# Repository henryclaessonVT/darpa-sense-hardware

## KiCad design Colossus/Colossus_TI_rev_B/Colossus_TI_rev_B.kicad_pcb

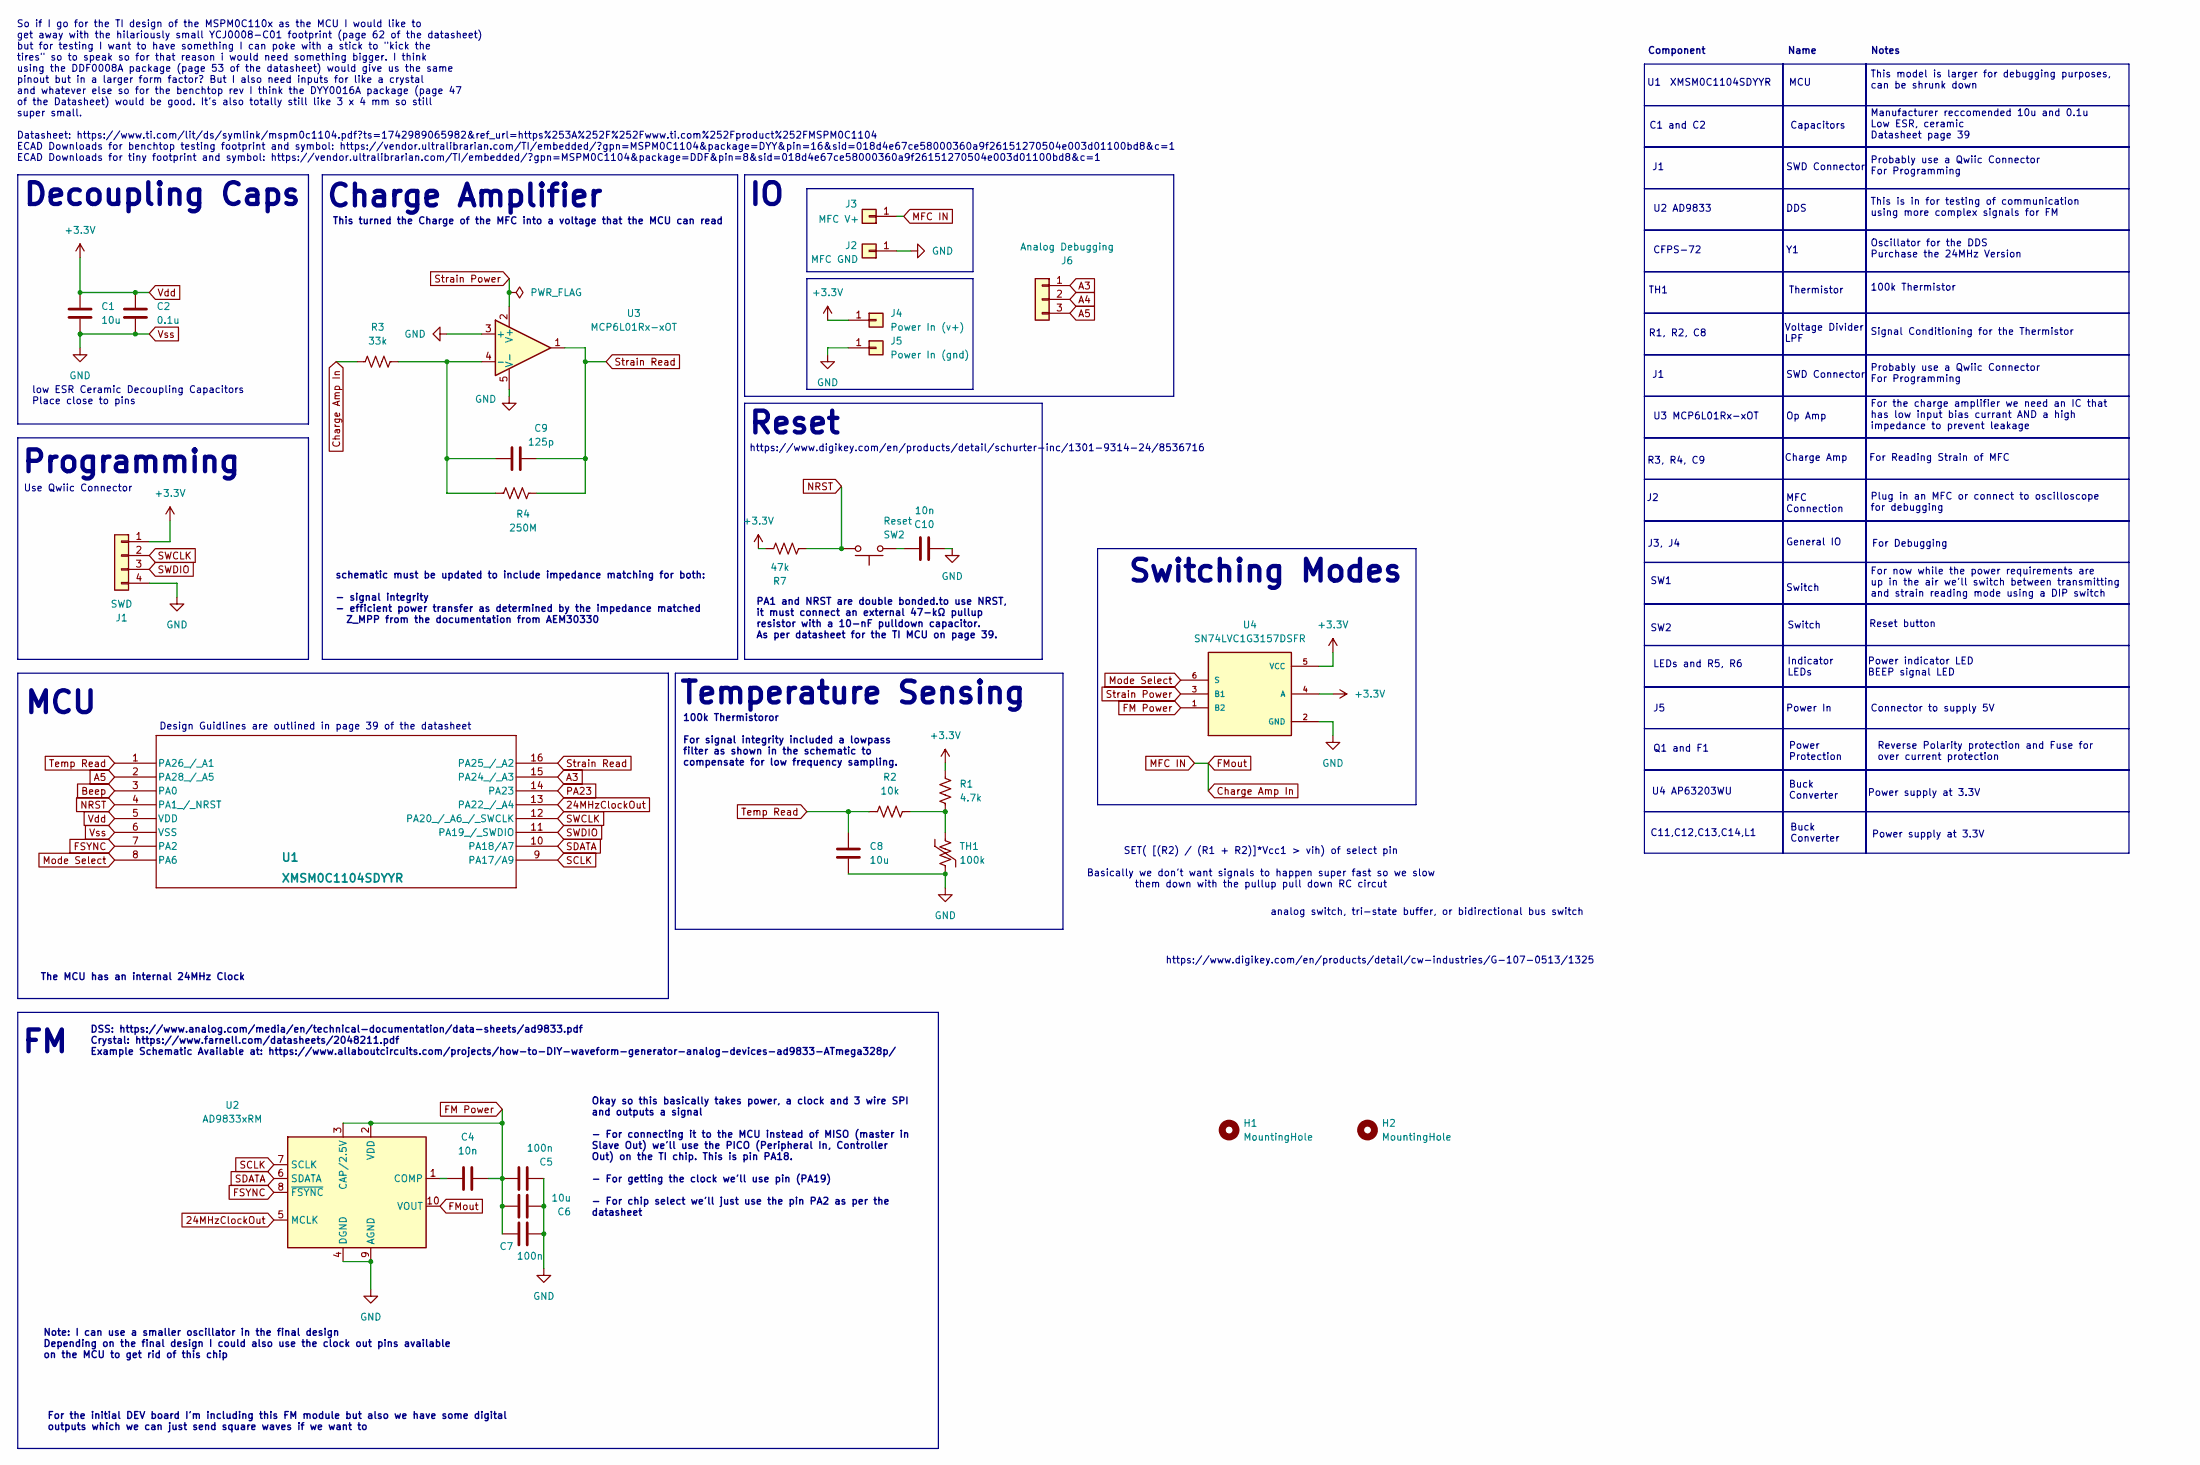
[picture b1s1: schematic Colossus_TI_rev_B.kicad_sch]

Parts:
C1, C6, C8: 10u; C_0402_1005Metric
C2: 0.1u; C_0201_0603Metric
C4: 10n; C_0201_0603Metric
C5, C7: 100n; C_0201_0603Metric
C9: 125p; C_0201_0603Metric
C10: 10n; C_0805_2012Metric
H1, H2: MountingHole; MountingHole_2.2mm_M2_Pad_Via
J1: SWD; PinHeader_1x04_P2.54mm_Vertical
J2: MFC GND; TestPoint_Pad_2.0x2.0mm
J3: MFC V+; TestPoint_Pad_2.0x2.0mm
J4: Power In (v+); TestPoint_Pad_2.0x2.0mm
J5: Power In (gnd); TestPoint_Pad_2.0x2.0mm
J6: Analog Debugging; PinSocket_1x03_P2.54mm_Vertical
R1: 4.7k; R_0201_0603Metric
R2: 10k; R_0201_0603Metric
R3: 33k; R_0201_0603Metric
R4: 250M; R_0402_1005Metric
R7: 47k; R_0805_2012Metric
SW2: Reset; SW_B3F-1000_OMR
TH1: 100k; R_0402_1005Metric
U1: XMSM0C1104SDYYR; SOT-23-THIN16_DYY_TEX
U2: AD9833xRM; MSOP-10_3x3mm_P0.5mm
U3: MCP6L01Rx-xOT; SOT-23-5
U4: SN74LVC1G3157DSFR; SON35P100X100X40-6N; PARTREV M

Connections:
24MHzClockOut: U1.13 (PA22_/_A4), U2.5 (MCLK)
A3: J6.1, U1.15 (PA24_/_A3)
A4: J6.2
A5: J6.3, U1.2 (PA28_/_A5)
Beep: U1.3 (PA0)
Charge Amp In: J3.1, R3.1, U2.10 (VOUT)
FM Power: C4.2, C5.2, C6.2, C7.1, U2.2 (VDD), U2.3 (CAP/2.5V), U4.1 (B2)
FSYNC: U1.7 (PA2), U2.8 (~FSYNC)
Mode Select: U1.8 (PA6), U4.6 (S)
NRST: R7.2, SW2.2, U1.4 (PA1_/_NRST)
unnamed: C10.2, SW2.1
unnamed: R1.2, R2.2, TH1.2
unnamed: C4.1, U2.1 (COMP)
unnamed: C9.1, R3.2, R4.1, U3.4 (-)
PA23: U1.14 (PA23)
SCLK: U1.9 (PA17/A9), U2.7 (SCLK)
SDATA: U1.10 (PA18/A7), U2.6 (SDATA)
SWCLK: J1.2, U1.12 (PA20_/_A6_/_SWCLK)
SWDIO: J1.3, U1.11 (PA19_/_SWDIO)
Strain Power: U3.2 (V+), U4.3 (B1)
Strain Read: C9.2, R4.2, U1.16 (PA25_/_A2), U3.1
Temp Read: C8.2, R2.1, U1.1 (PA26_/_A1)
Vdd: C1.1, C2.1, J1.1, J4.1, R1.1, R7.1, U1.5 (VDD), U4.4 (A), U4.5 (VCC)
Vss: C1.2, C2.2, C5.1, C6.1, C7.2, C8.1, C10.1, J1.4, J2.1, J5.1, TH1.1, U1.6 (VSS), U2.4 (DGND), U2.9 (AGND), U3.3 (+), U3.5 (V-), U4.2 (GND)

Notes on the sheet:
J3, J4
TH1
Buck Converter
DDS
For the initial DEV board I'm including this FM module but also we have some digital outputs which we can just send square waves if we want to
Notes
Power supply at 3.3V
Charge Amp
Design Guidlines are outlined in page 39 of the datasheet
Note: I can use a smaller oscillator in the final design Depending on the final design I could also use the clock out pins available on the MCU to get rid of this chip
Switch
low ESR Ceramic Decoupling Capacitors Place close to pins
C1 and C2
For the charge amplifier we need an IC that has low input bias currant AND a high impedance to prevent leakage
Power indicator LED BEEP signal LED
Temperature Sensing
Plug in an MFC or connect to oscilloscope for debugging
Voltage Divider LPF
U4 AP63203WU
General IO
Power Protection
analog switch, tri-state buffer, or bidirectional bus switch
Probably use a Qwiic Connector For Programming
For now while the power requirements are up in the air we'll switch between transmitting and strain reading mode using a DIP switch
Programming
U2 AD9833
Charge Amplifier
Manufacturer reccomended 10u and 0.1u Low ESR, ceramic Datasheet page 39
This turned the Charge of the MFC into a voltage that the MCU can read
schematic must be updated to include impedance matching for both: - signal integrity - efficient power transfer as determined by the impedance matched Z_MPP from the documentation from AEM30330
Switching Modes
Name
Power In
C11,C12,C13,C14,L1
Decoupling Caps
Capacitors
Connector to supply 5V
Use Qwiic Connector
SET( [(R2) / (R1 + R2)]*Vcc1 > vih) of select pin Basically we don't want signals to happen super fast so we slow them down with the pullup pull down RC circut
Component

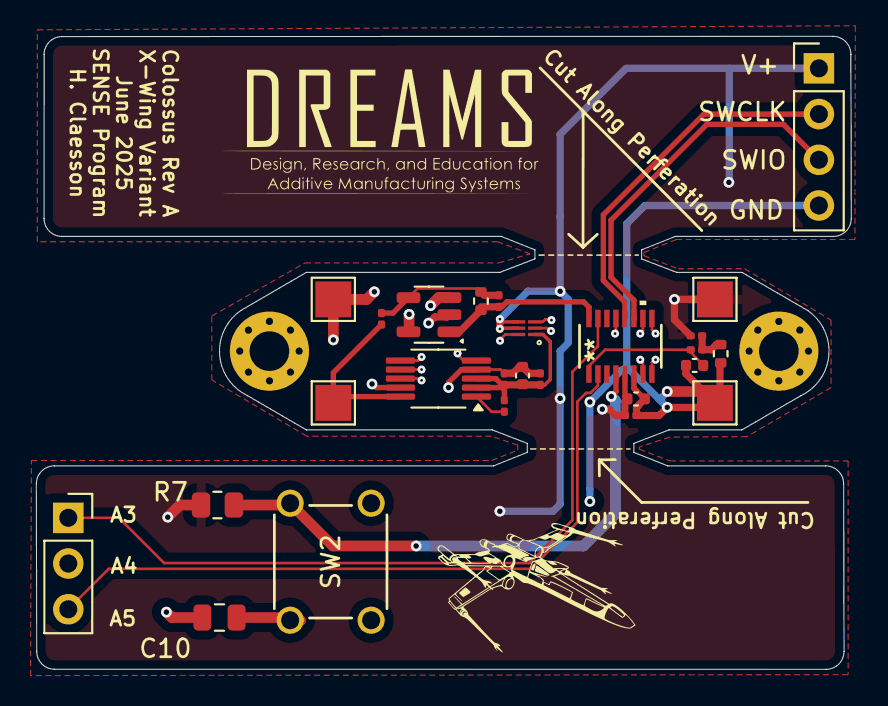
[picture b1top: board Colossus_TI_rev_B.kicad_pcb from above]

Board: 4 copper layers, 45.3 x 35.2 mm, 28 parts (0 on the bottom side), 21 nets.

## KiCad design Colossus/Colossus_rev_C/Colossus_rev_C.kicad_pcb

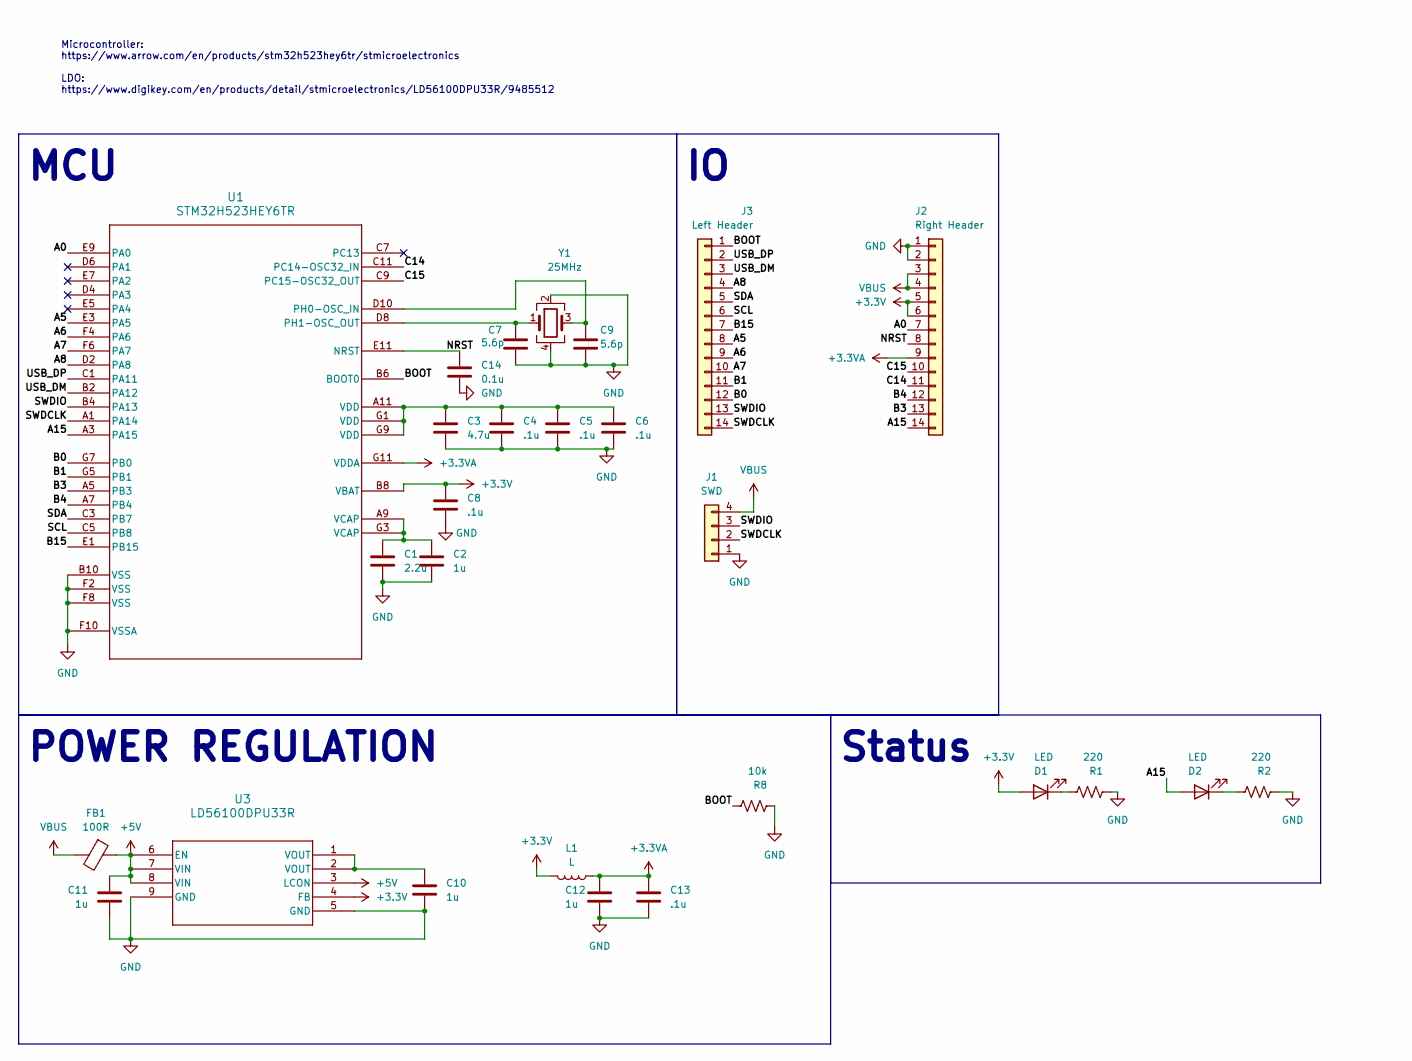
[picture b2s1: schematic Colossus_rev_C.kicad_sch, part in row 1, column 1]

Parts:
C1: 2.2u; C_0201_0603Metric
C2, C10, C11, C12: 1u; C_0201_0603Metric
C3: 4.7u; C_0201_0603Metric
C4, C5, C6, C8, C13: .1u; C_0201_0603Metric
C7, C9: 5.6p; C_0201_0603Metric
C14: 0.1u; C_0201_0603Metric
D1, D2: LED; LED_0201_0603Metric
FB1: 100R; LED_0201_0603Metric
J1: SWD; PinHeader_1x04_P1.00mm_Vertical
J2: Right Header; PinHeader_1x14_P1.27mm_Vertical
J3: Left Header; PinHeader_1x14_P1.27mm_Vertical
L1: L; L_0201_0603Metric
R1, R2: 220; R_01005_0402Metric
R8: 10k; R_01005_0402Metric
U1: STM32H523HEY6TR; WLCSP39_STM
U3: LD56100DPU33R; DFN8_1P6X1P2_STM-M
Y1: 25MHz; Oscillator_SMD_Abracon_ASCO-4Pin_1.6x1.2mm

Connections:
+3.3V: C8.1, D1.2 (A), J2.5, J2.6, L1.2, U1.B8 (VBAT), U3.4 (FB)
+3.3VA: C12.1, C13.1, J2.9, L1.1, U1.G11 (VDDA)
+5V: C11.1, FB1.1, U3.3 (LCON), U3.6 (EN), U3.7 (VIN), U3.8 (VIN)
/A0: J2.7, U1.E9 (PA0)
/A5: J3.8, U1.E3 (PA5)
/A6: J3.9, U1.F4 (PA6)
/A7: J3.10, U1.F6 (PA7)
/A8: J3.4, U1.D2 (PA8)
/A15: D2.2 (A), J2.14, U1.A3 (PA15)
/B0: J3.12, U1.G7 (PB0)
/B1: J3.11, U1.G5 (PB1)
/B3: J2.13, U1.A5 (PB3)
/B4: J2.12, U1.A7 (PB4)
/B15: J3.7, U1.E1 (PB15)
/BOOT: J3.1, R8.1, U1.B6 (BOOT0)
/C14: J2.11, U1.C11 (PC14-OSC32_IN)
/C15: J2.10, U1.C9 (PC15-OSC32_OUT)
/NRST: C14.1, J2.8, U1.E11 (NRST)
/SCL: J3.6, U1.C5 (PB8)
/SDA: J3.5, U1.C3 (PB7)
/SWDCLK: J1.2, J3.14, U1.A1 (PA14)
/SWDIO: J1.3, J3.13, U1.B4 (PA13)
/USB_DM: J3.3, U1.B2 (PA12)
/USB_DP: J3.2, U1.C1 (PA11)
GND: C1.2, C2.2, C3.2, C4.2, C5.2, C6.2, C7.2, C8.2, C9.2, C10.2, C11.2, C12.2, C13.2, C14.2, J1.1, J2.1, J2.2, R1.2, R2.2, R8.2, U1.B10 (VSS), U1.F2 (VSS), U1.F8 (VSS), U1.F10 (VSSA), U3.5 (GND), U3.9 (GND), Y1.2, Y1.4
unnamed: C1.1, C2.1, U1.A9 (VCAP), U1.G3 (VCAP)
unnamed: C3.1, C4.1, C5.1, C6.1, U1.A11 (VDD), U1.G1 (VDD), U1.G9 (VDD)
unnamed: C10.1, U3.1 (VOUT), U3.2 (VOUT)
unnamed: D1.1 (K), R1.1
unnamed: D2.1 (K), R2.1
unnamed: C9.1, U1.D10 (PH0-OSC_IN), Y1.3
unnamed: C7.1, U1.D8 (PH1-OSC_OUT), Y1.1
VBUS: FB1.2, J1.4, J2.3, J2.4

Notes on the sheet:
TODO: x Temperature Sensing Circuit o Strain Sensing Circuit -- skip this rev x IMU Circuit - MFC Communication Out Circuit - MFC Communication In Circuit - Energy Harvesting Circuit After that -- layout
Microcontroller: https://www.arrow.com/en/products/stm32h523hey6tr/stmicroelectronics LDO: https://www.digikey.com/en/products/detail/stmicroelectronics/LD56100DPU33R/9485512
MCU
POWER REGULATION
Status

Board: 2 copper layers, 27 parts (0 on the bottom side), 33 nets, no tracks yet.

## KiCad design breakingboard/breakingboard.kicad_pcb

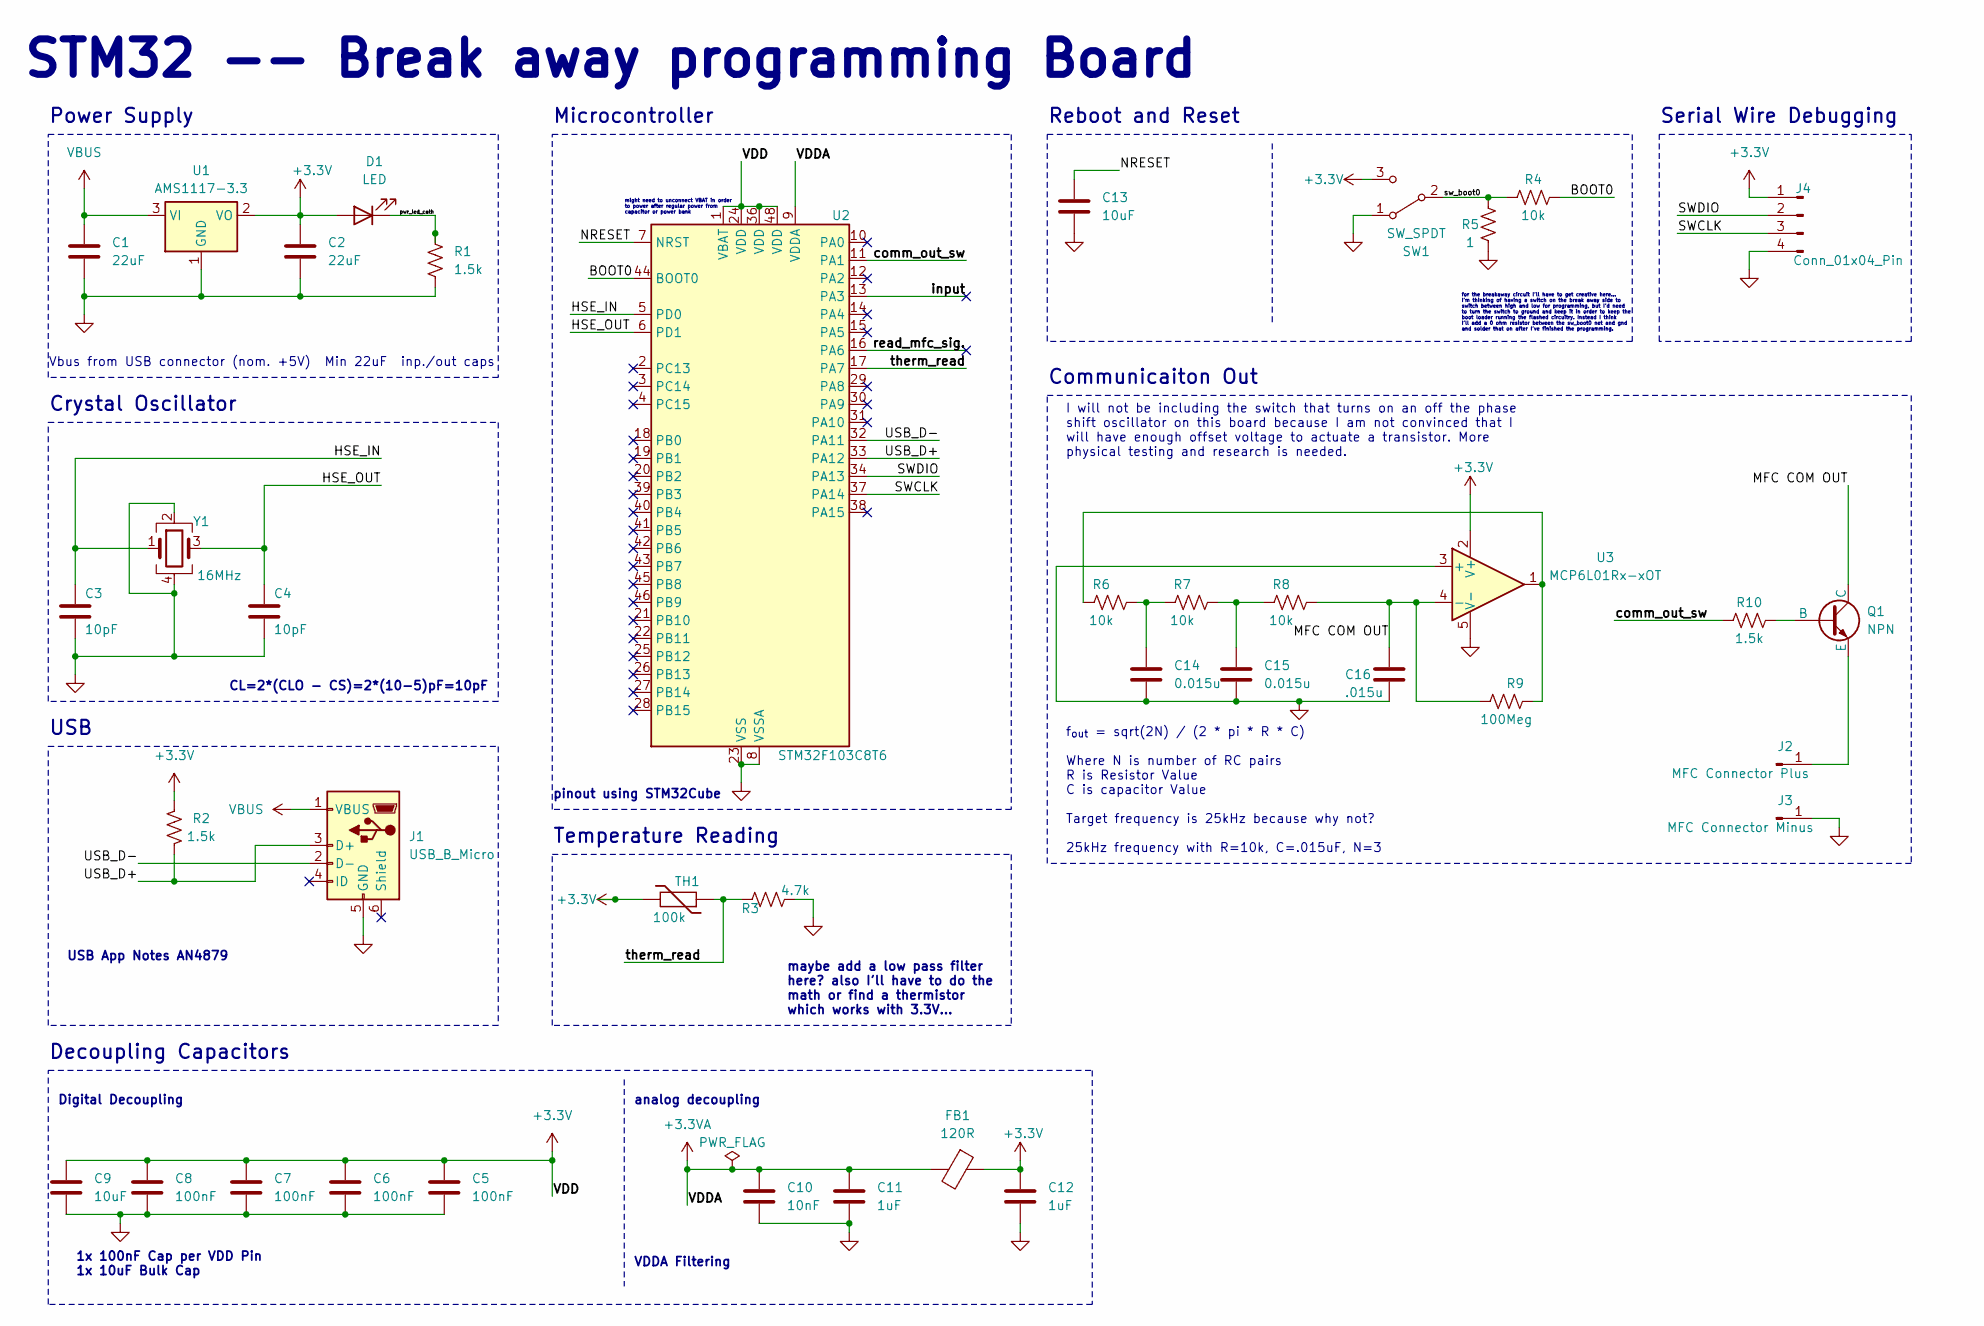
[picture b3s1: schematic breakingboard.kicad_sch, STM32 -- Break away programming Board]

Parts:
C1, C2: 22uF; C_0805_2012Metric
C3, C4: 10pF; C_0402_1005Metric
C5, C6, C7, C8: 100nF; C_0402_1005Metric
C9, C13: 10uF; C_0603_1608Metric
C10: 10nF; C_0402_1005Metric
C11, C12: 1uF; C_0402_1005Metric
C14, C15: 0.015u; C_0402_1005Metric
C16: .015u; C_0402_1005Metric
D1: LED; LED_0402_1005Metric
FB1: 120R; L_0603_1608Metric
J1: USB_B_Micro; USB_Micro-B_Wuerth_629105150521
J2: MFC Connector Plus; SolderWire-0.1sqmm_1x01_D0.4mm_OD1mm
J3: MFC Connector Minus; SolderWire-0.1sqmm_1x01_D0.4mm_OD1mm
J4: Conn_01x04_Pin; PinHeader_1x04_P2.54mm_Vertical
Q1: NPN; SOT-23
R1, R2, R10: 1.5k; R_0402_1005Metric
R3: 4.7k; R_0402_1005Metric
R4, R6, R7, R8: 10k; R_0402_1005Metric
R5: 1; R_0402_1005Metric
R9: 100Meg; R_0402_1005Metric
SW1: SW_SPDT; SW_SPDT_PCM12
TH1: 100k; R_0402_1005Metric
U1: AMS1117-3.3; SOT-223-3_TabPin2
U2: STM32F103C8T6; LQFP-48_7x7mm_P0.5mm
U3: MCP6L01Rx-xOT; SOT-23-5
Y1: 16MHz; Crystal_SMD_3225-4Pin_3.2x2.5mm

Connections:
+3.3V: C2.1, C5.1, C6.1, C7.1, C8.1, C9.1, C12.1, D1.2 (A), FB1.1, J4.1, R2.2, SW1.3 (C), TH1.2, U1.2 (VO), U2.1 (VBAT), U2.24 (VDD), U2.36 (VDD), U2.48 (VDD), U3.2 (V+)
+3.3VA: C10.1, C11.1, FB1.2, U2.9 (VDDA)
/BOOT0: R4.2, U2.44 (BOOT0)
/HSE_IN: C3.1, U2.5 (PD0), Y1.1
/HSE_OUT: C4.1, U2.6 (PD1), Y1.3
/MFC COM OUT: C16.1, Q1.1 (C), R8.2, R9.1, U3.4 (-)
/NRESET: C13.1, U2.7 (NRST)
/SWCLK: J4.3, U2.37 (PA14)
/SWDIO: J4.2, U2.34 (PA13)
/USB_D+: J1.3 (D+), R2.1, U2.33 (PA12)
/USB_D-: J1.2 (D-), U2.32 (PA11)
/comm_out_sw: R10.1, U2.11 (PA1)
/input: U2.13 (PA3)
/pwr_led_cath: D1.1 (K), R1.1
/read_mfc_sig.: U2.16 (PA6)
/sw_boot0: R4.1, R5.2, SW1.2 (B)
/therm_read: R3.2, TH1.1, U2.17 (PA7)
GND: C1.2, C2.2, C3.2, C4.2, C5.2, C6.2, C7.2, C8.2, C9.2, C10.2, C11.2, C12.2, C13.2, C14.2, C15.2, C16.2, J1.5 (GND), J3.1, J4.4, R1.2, R3.1, R5.1, SW1.1 (A), U1.1 (GND), U2.8 (VSSA), U2.23 (VSS), U2.35 (VSS), U2.47 (VSS), U3.3 (+), U3.5 (V-), Y1.2, Y1.4
unnamed: C14.1, R6.2, R7.1
unnamed: C15.1, R7.2, R8.1
unnamed: J2.1, Q1.3 (E)
unnamed: Q1.2 (B), R10.2
unnamed: R6.1, R9.2, U3.1
VBUS: C1.1, J1.1 (VBUS), U1.3 (VI)

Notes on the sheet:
VDDA Filtering
might need to unconnect VBAT in order to power after regular power from capacitor or power bank
CL=2*(CLO - CS)=2*(10-5)pF=10pF
Microcontroller
Temperature Reading
Serial Wire Debugging
maybe add a low pass filter here? also I'll have to do the math or find a thermistor which works with 3.3V...
Reboot and Reset
I will not be including the switch that turns on an off the phase shift oscillator on this board because I am not convinced that I will have enough offset voltage to actuate a transistor. More physical testing and research is needed.
Communicaiton Out
Decoupling Capacitors
for the breakaway circuit I'll have to get creative here... I'm thinking of having a switch on the break away side to switch between high and low for programming, but I'd need to turn the switch to ground and keep it in order to keep the boot loader running the flashed circuitry. Instead I think I'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
f_{out} = sqrt(2N) / (2 * pi * R * C) Where N is number of RC pairs R is Resistor Value C is capacitor Value Target frequency is 25kHz because why not? 25kHz frequency with R=10k, C=.015uF, N=3
pinout using STM32Cube
Crystal Oscillator
Power Supply
1x 100nF Cap per VDD Pin 1x 10uF Bulk Cap
STM32 -- Break away programming Board
Digital Decoupling
analog decoupling
USB
Vbus from USB connector (nom. +5V) Min 22uF inp./out caps
USB App Notes AN4879

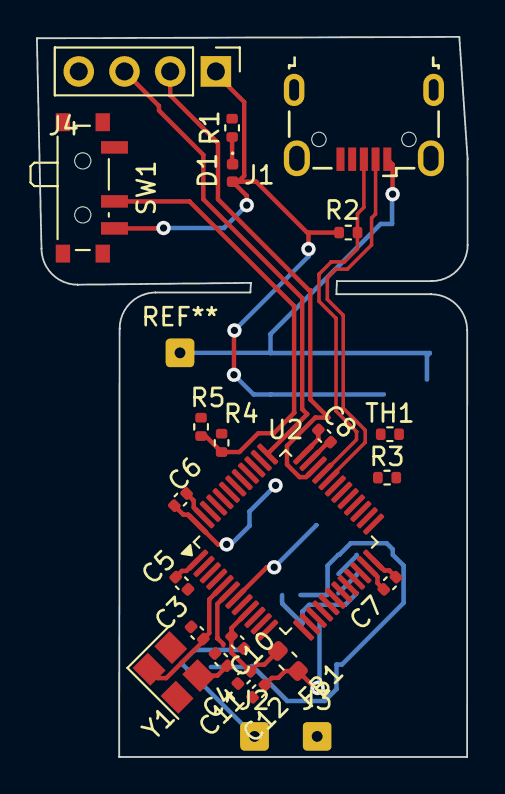
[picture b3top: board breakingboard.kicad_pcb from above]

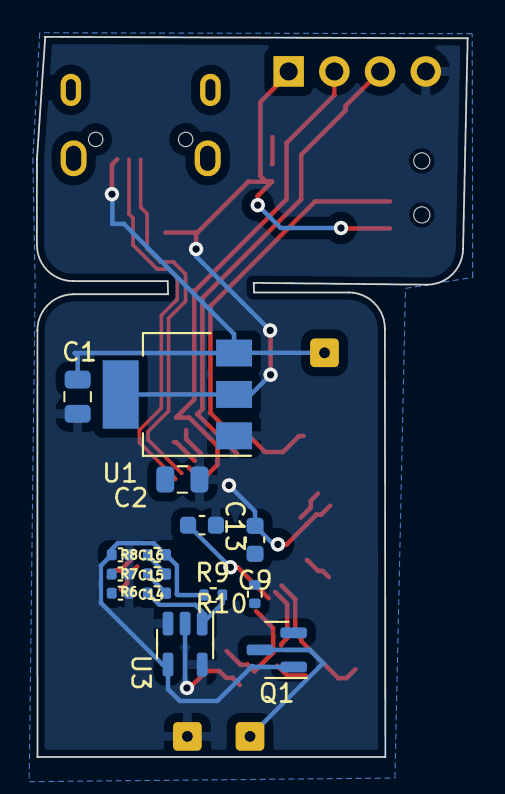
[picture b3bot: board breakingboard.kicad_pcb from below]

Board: 2 copper layers, 23.9 x 40.0 mm, 39 parts (15 on the bottom side), 22 nets.

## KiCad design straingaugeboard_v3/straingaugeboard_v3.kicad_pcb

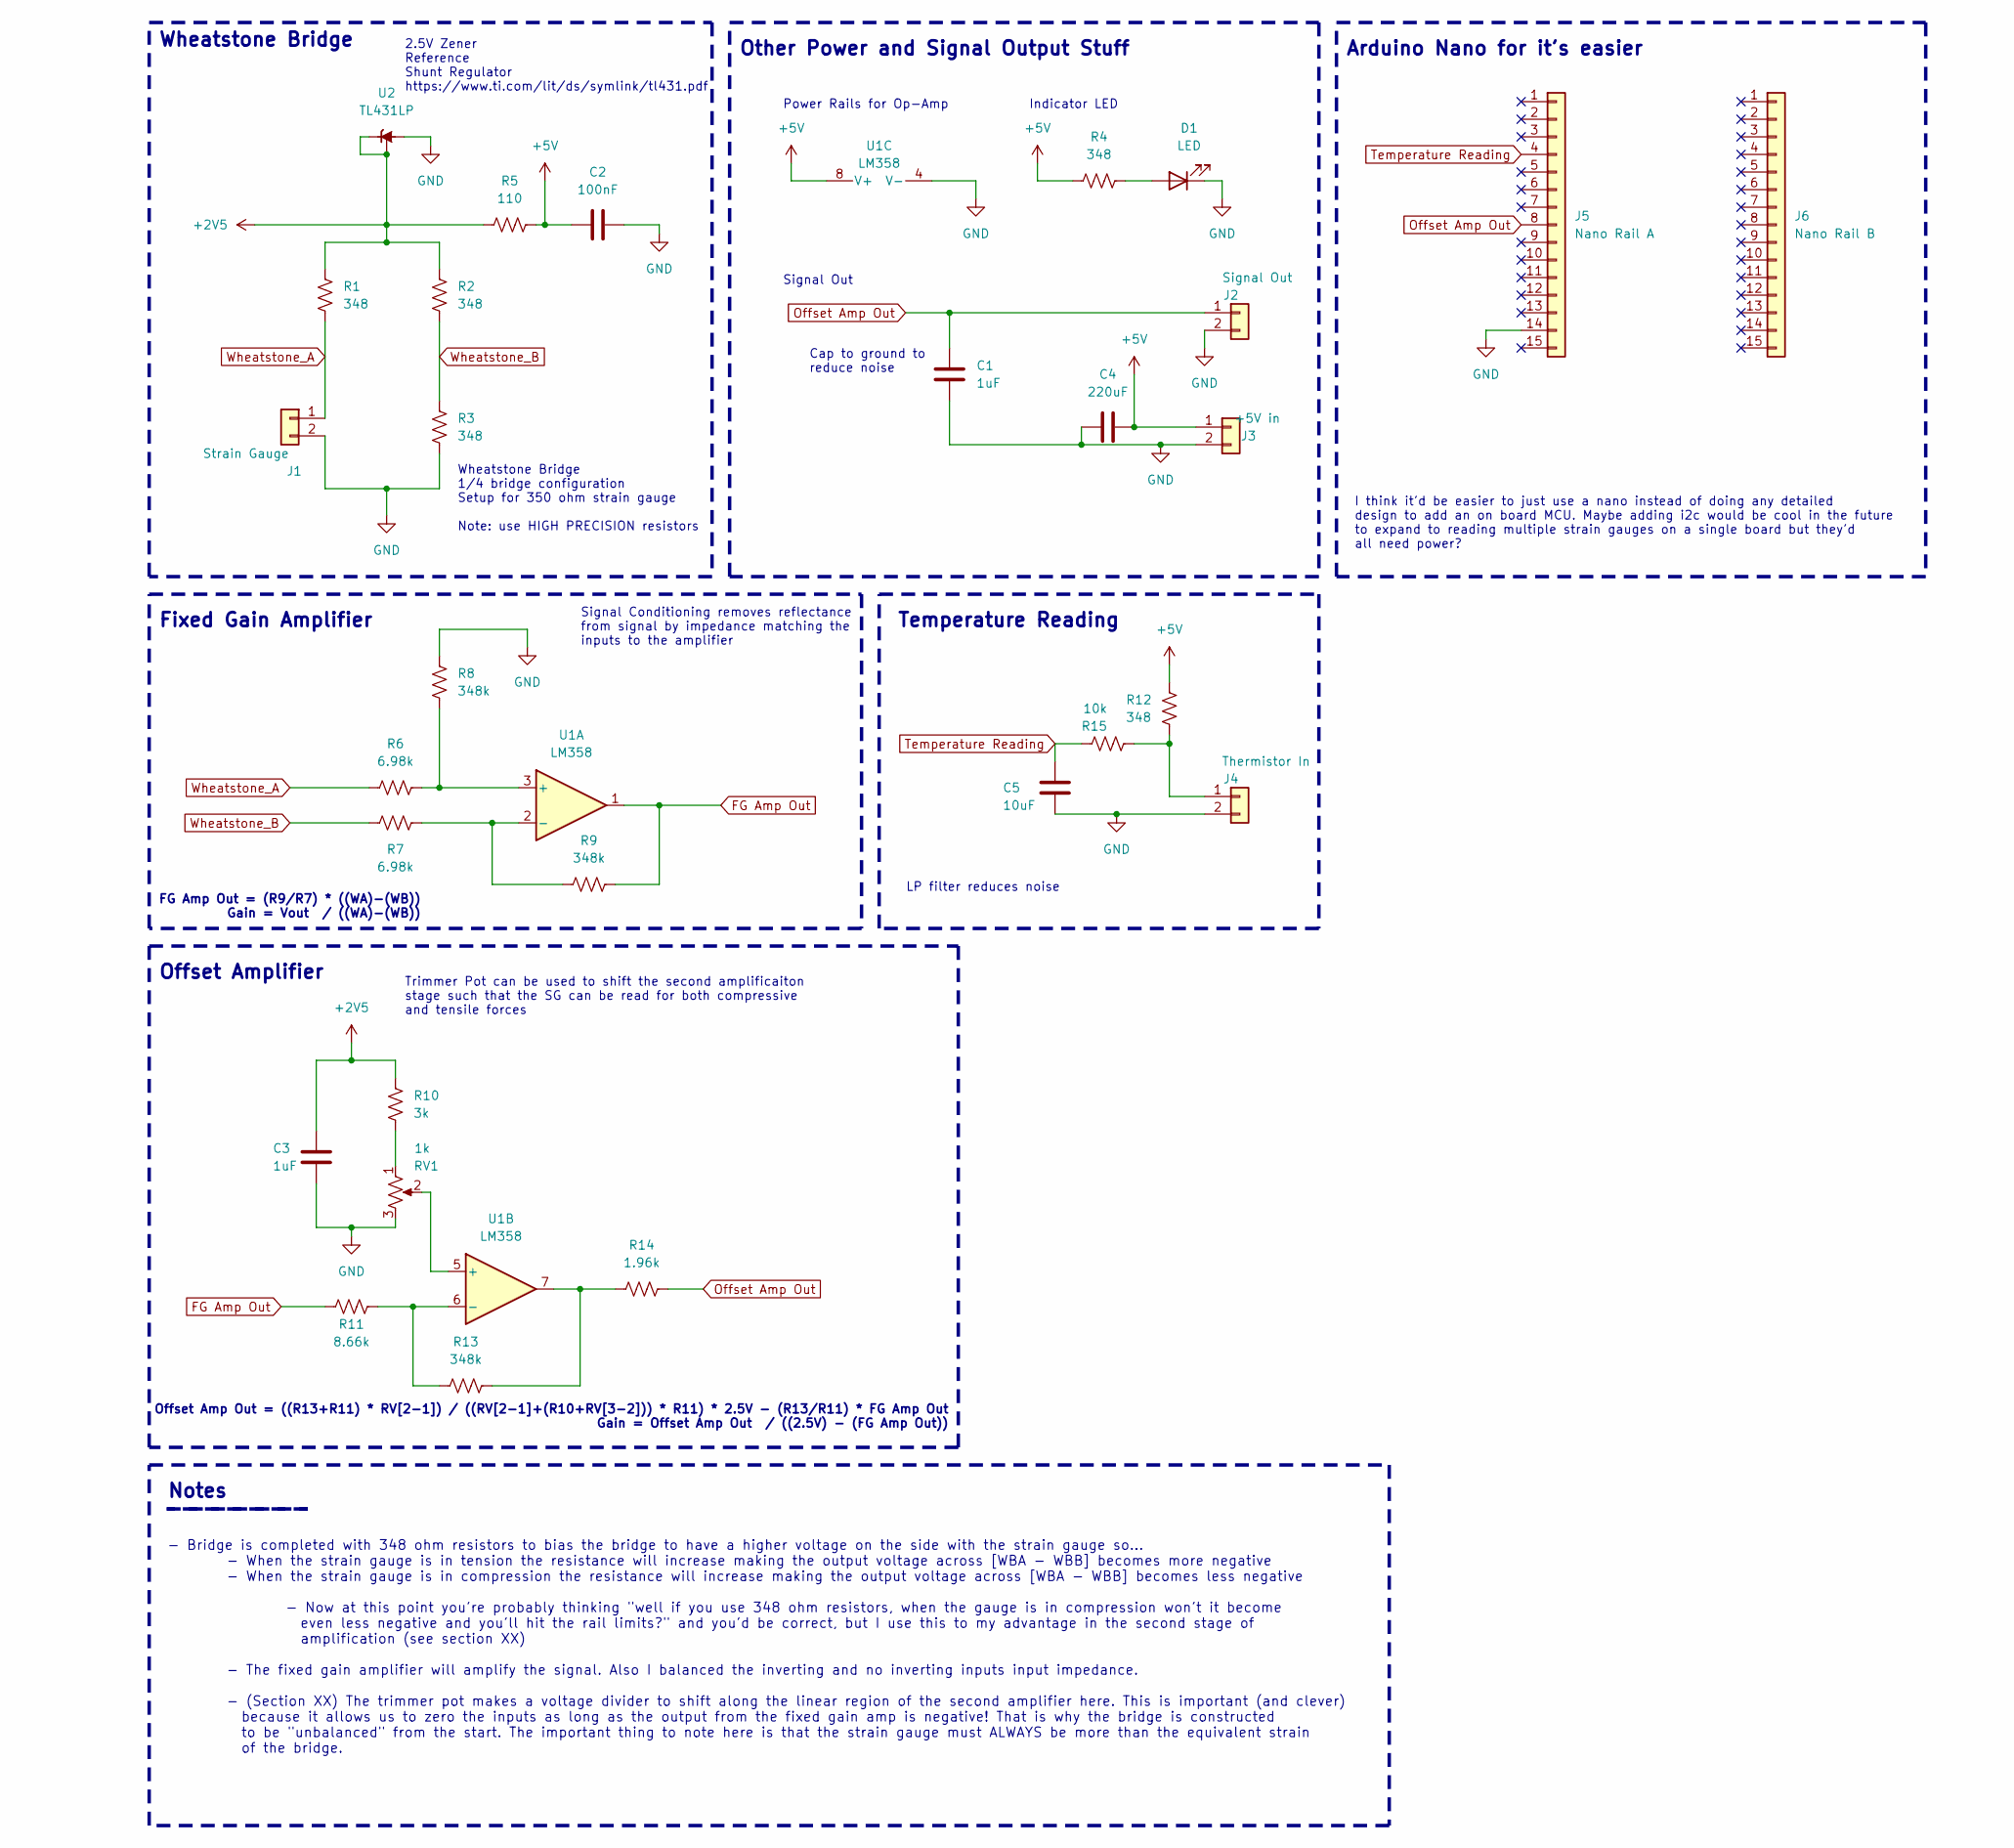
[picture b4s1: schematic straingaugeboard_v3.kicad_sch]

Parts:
C1, C3: 1uF; C_1206_3216Metric
C2: 100nF; C_1206_3216Metric
C4: 220uF; C_1206_3216Metric
C5: 10uF; C_1206_3216Metric
D1: LED; LED_1206_3216Metric
J1: Strain Gauge; TerminalBlock_Phoenix_MKDS-1,5-2-5.08_1x02_P5.08mm_Horizont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
J2: Signal Out; TerminalBlock_Phoenix_MKDS-1,5-2-5.08_1x02_P5.08mm_Horizont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
J3: +5V in; BarrelJack_CUI_PJ-063AH_Horizontal
J4: Thermistor In; TerminalBlock_Phoenix_MKDS-1,5-2-5.08_1x02_P5.08mm_Horizont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
J5: Nano Rail A; PinSocket_1x15_P2.54mm_Vertical
J6: Nano Rail B; PinSocket_1x15_P2.54mm_Vertical
R1: 348; LED_1206_3216Metric
R2, R3, R4, R12: 348; R_1206_3216Metric
R5: 110; R_1206_3216Metric
R6, R7: 6.98k; R_1206_3216Metric
R8, R9, R13: 348k; R_1206_3216Metric
R10: 3k; R_1206_3216Metric
R11: 8.66k; R_1206_3216Metric
R14: 1.96k; R_1206_3216Metric
R15: 10k; R_1206_3216Metric
RV1: 1k; Potentiometer_Bourns_3266Y_Vertical
U1: LM358; DIP-8_W7.62mm
U2: TL431LP; TO-92_Inline

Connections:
+2V5: C3.1, R1.1, R2.1, R5.1, R10.1, U2.1 (REF), U2.3 (K)
+5V: C2.1, C4.2, J3.1, R4.1, R5.2, R12.1, U1.8 (V+)
FG Amp Out: R9.1, R11.1, U1.1
GND: C1.2, C2.2, C3.2, C4.1, C5.1, D1.1 (K), J1.2, J2.2, J3.2, J4.2, J5.14, R3.2, R8.2, RV1.3, U1.4 (V-), U2.2 (A)
unnamed: D1.2 (A), R4.2
unnamed: J4.1, R12.2, R15.2
unnamed: R10.2, RV1.1
unnamed: R13.1, R14.2, U1.7
unnamed: R6.2, R8.1, U1.3 (+)
unnamed: R7.2, R9.2, U1.2 (-)
unnamed: RV1.2, U1.5 (+)
unnamed: R11.2, R13.2, U1.6 (-)
Offset Amp Out: C1.1, J2.1, J5.8, R14.1
Temperature Reading: C5.2, J5.4, R15.1
Wheatstone_A: J1.1, R1.2, R6.1
Wheatstone_B: R2.2, R3.1, R7.1

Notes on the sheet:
- Bridge is completed with 348 ohm resistors to bias the bridge to have a higher voltage on the side with the strain gauge so... - When the strain gauge is in tension the resistance will increase making the output voltage across [WBA - WBB] becomes more negative - When the strain gauge is in compre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
Cap to ground to reduce noise
Offset Amplifier
Fixed Gain Amplifier
Wheatstone Bridge 1/4 bridge configuration Setup for 350 ohm strain gauge Note: use HIGH PRECISION resistors
FG Amp Out = (R9/R7) * ((WA)-(WB)) Gain = Vout / ((WA)-(WB))
Arduino Nano for it's easier
2.5V Zener Reference Shunt Regulator https://www.ti.com/lit/ds/symlink/tl431.pdf
Signal Out
Signal Conditioning removes reflectance from signal by impedance matching the inputs to the amplifier
Indicator LED
Trimmer Pot can be used to shift the second amplificaiton stage such that the SG can be read for both compressive and tensile forces
Notes
Other Power and Signal Output Stuff
I think it'd be easier to just use a nano instead of doing any detailed design to add an on board MCU. Maybe adding i2c would be cool in the future to expand to reading multiple strain gauges on a single board but they'd all need power?
Temperature Reading
Offset Amp Out = ((R13+R11) * RV[2-1]) / ((RV[2-1]+(R10+RV[3-2])) * R11) * 2.5V - (R13/R11) * FG Amp Out Gain = Offset Amp Out / ((2.5V) - (FG Amp Out))
LP filter reduces noise
Power Rails for Op-Amp
Wheatstone Bridge

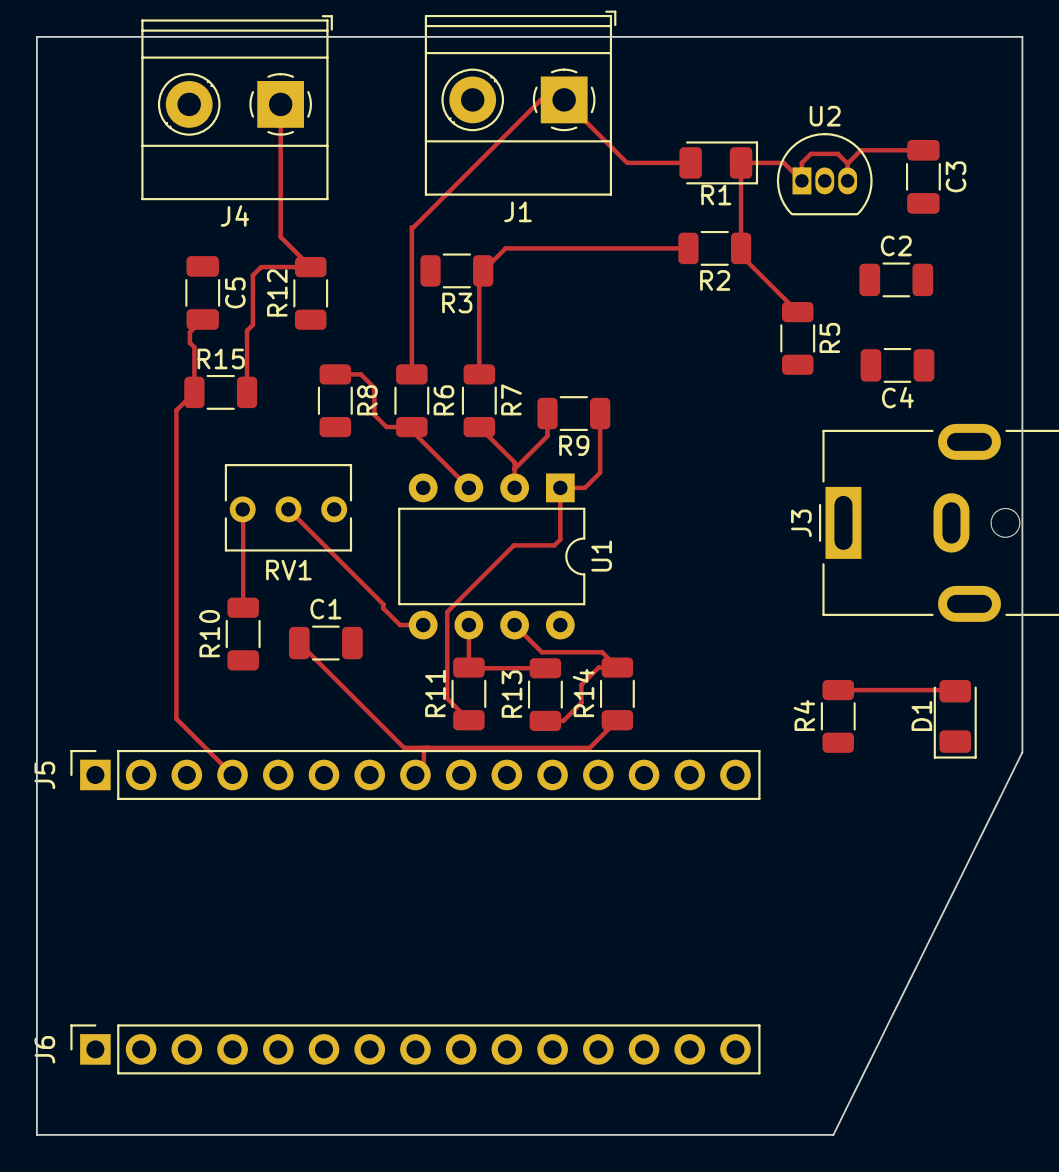
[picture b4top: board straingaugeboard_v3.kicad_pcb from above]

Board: 2 copper layers, 54.8 x 61.0 mm, 29 parts (0 on the bottom side), 16 nets.

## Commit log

2024-11-11 add my files
2025-01-02 pushing to save
2025-01-10 pushing
2025-03-21 pushing to desktop
2025-03-25 pushing for desktop
2025-04-02 adding ti board
2025-05-27 proto of rev b coloccus
2025-06-10 working on miniaturization
2025-06-12 pushing to take the trian to family day
2025-08-12 final and manufactured draft of revB board
